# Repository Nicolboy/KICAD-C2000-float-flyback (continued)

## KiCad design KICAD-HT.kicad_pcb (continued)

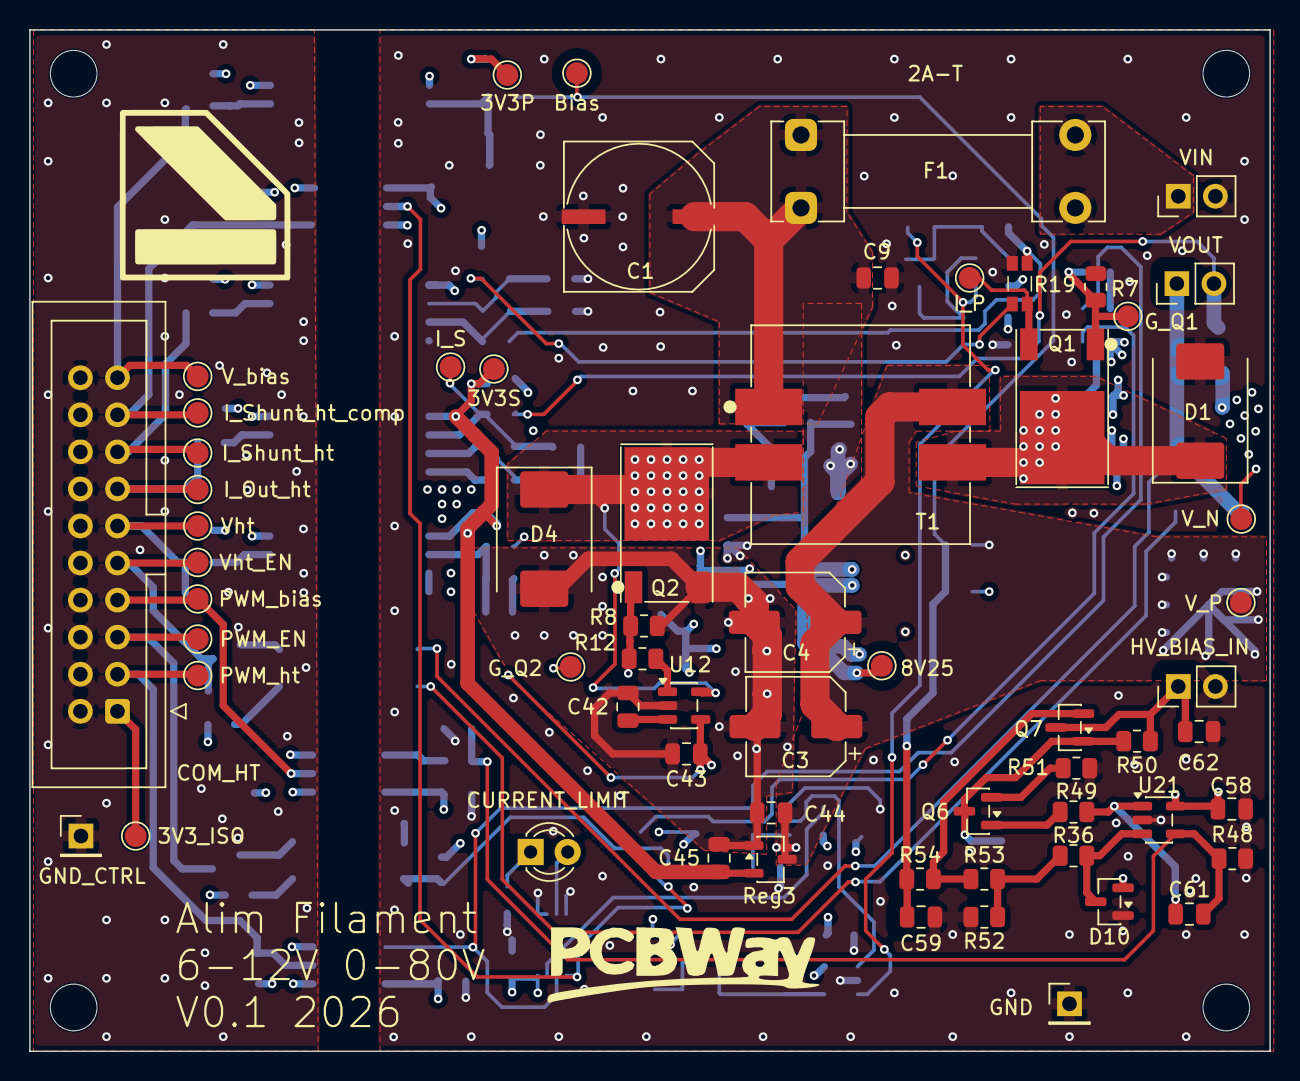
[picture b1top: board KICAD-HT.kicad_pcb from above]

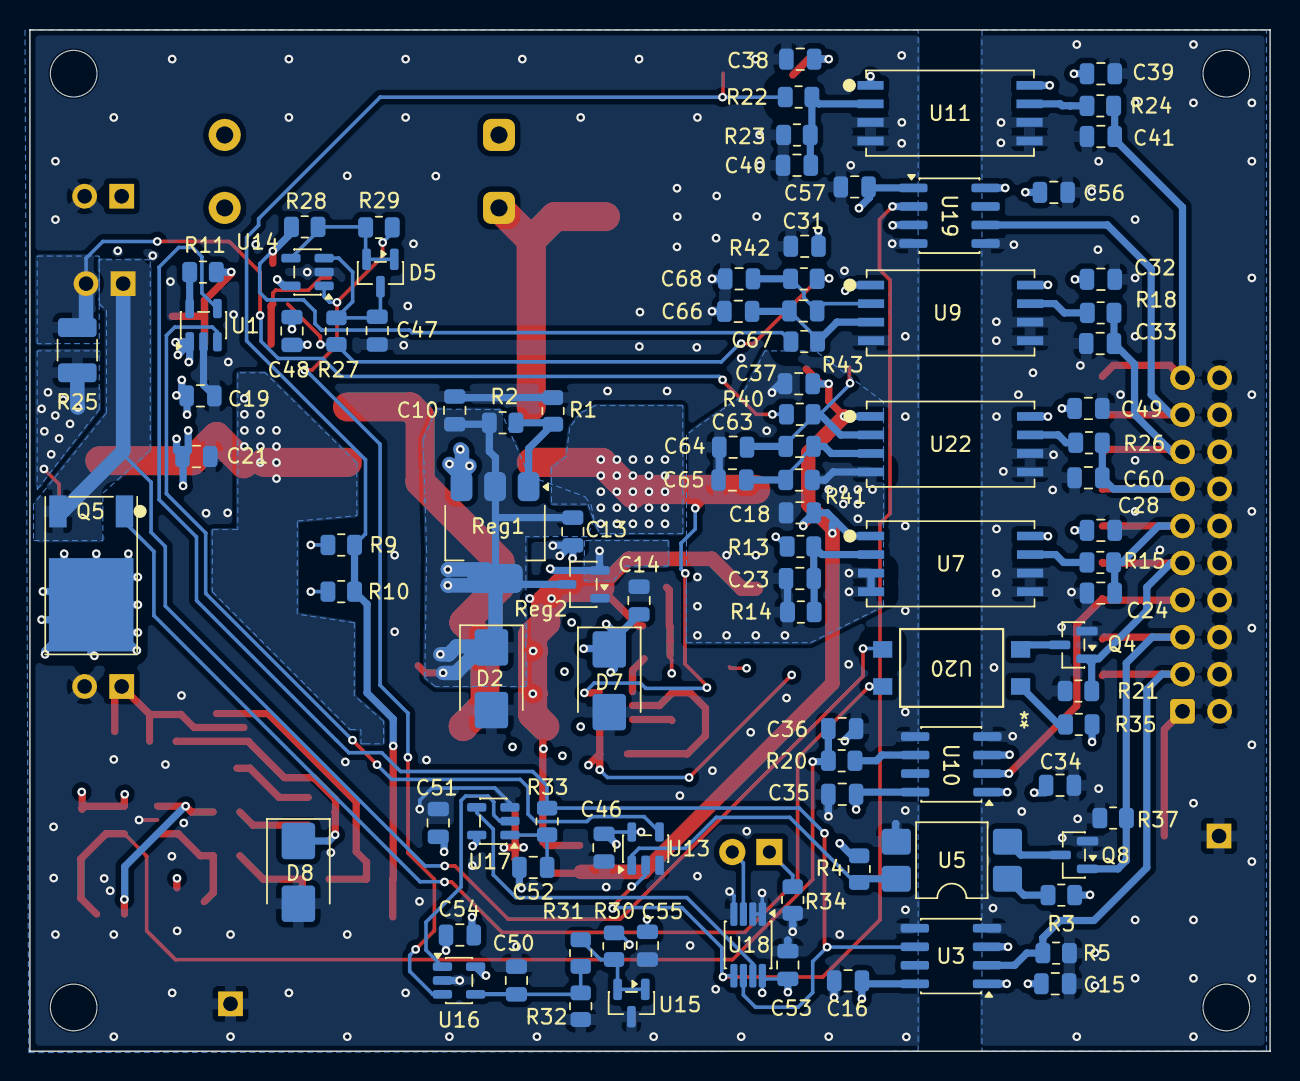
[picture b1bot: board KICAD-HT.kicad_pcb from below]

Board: 4 copper layers, 85.0 x 70.0 mm, 166 parts (99 on the bottom side), 72 nets.

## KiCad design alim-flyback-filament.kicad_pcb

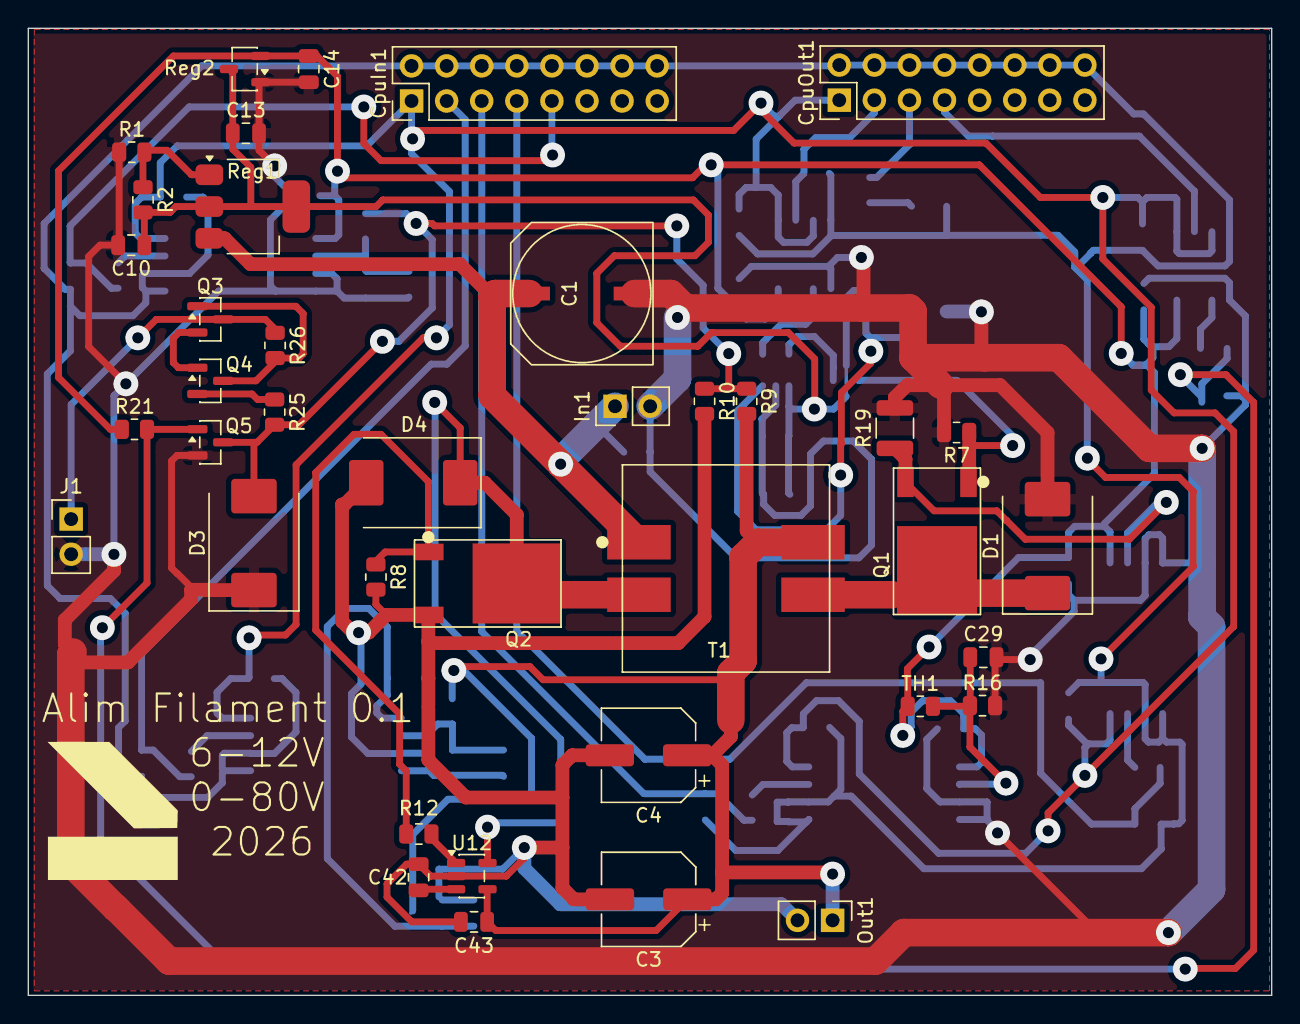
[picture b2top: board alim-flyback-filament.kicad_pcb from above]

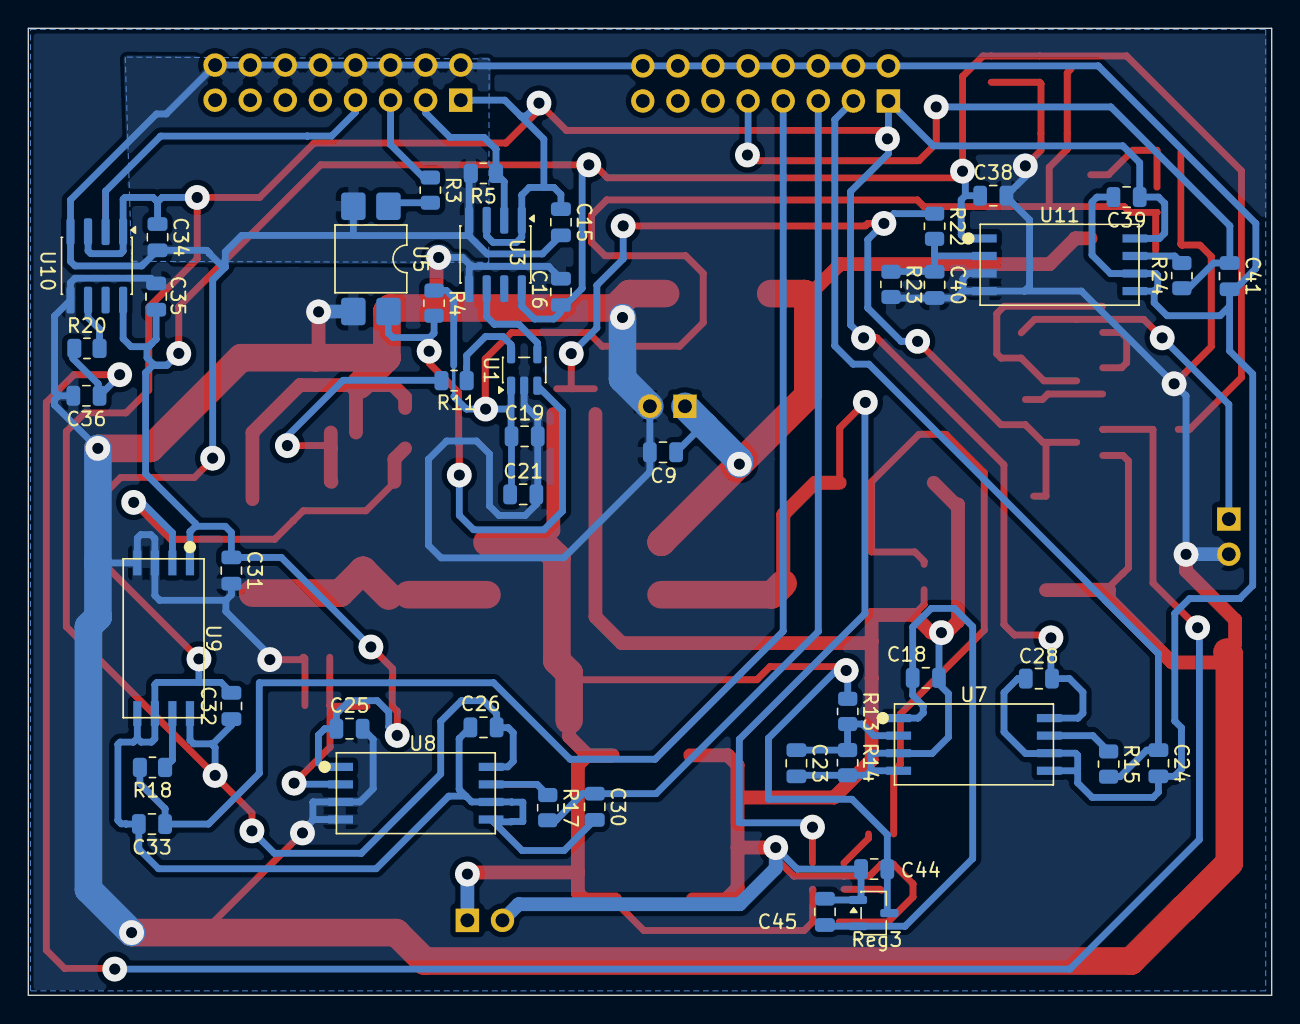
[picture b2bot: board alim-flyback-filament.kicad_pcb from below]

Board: 2 copper layers, 90.0 x 70.0 mm, 85 parts (46 on the bottom side), 42 nets.

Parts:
C1: 470u; A786MW_VChip
C3, C4: 330u; CP_Elec_6.3x9.9
C9, C13, C14, C44, C45: 1u; C_0805_2012Metric
C10, C21, C42: 10u; C_0805_2012Metric
C15, C16, C18, C19, C25, C26, C28, C31, C32, C34, C35, C36, C38, C39, C43: 100n; C_0805_2012Metric
C23, C29, C40: 100p; C_0805_2012Metric
C24, C30, C33, C41: 1n; C_0805_2012Metric
CpuIn1: CTRL_C2000_IN; PinHeader_2x08_P2.54mm_Vertical
CpuOut1: CTRL_C2000_OUT; PinHeader_2x08_P2.54mm_Vertical
D1: SMCJ43A; D_SMC
D3: SMCJ100A; D_SMC
D4: SMCJ54A; D_SMC
In1: VIN; PinHeader_1x02_P2.54mm_Vertical
J1: HV80_IN; PinHeader_1x02_P2.54mm_Vertical
Out1: VOUT; PinHeader_1x02_P2.54mm_Vertical
Q1, Q2: IPD050N10N5; TO252-3_TabPin2
Q3, Q5: BSS127I; SOT-23
Q4: MMBT2222; SOT-23
R1, R15, R17, R18, R24: 100; R_0805_2012Metric
R2: 560; R_0805_2012Metric
R3: 470; R_0805_2012Metric
R4, R14, R16, R20, R23: 10k; R_0805_2012Metric
R5, R7, R8, R9, R10: 100k; R_0805_2012Metric
R11, R12: 1; R_0805_2012Metric
R13: 51k; R_0805_2012Metric
R19: 7m5; R_1210_3225Metric
R21: 1M; R_0805_2012Metric
R22: 470k; R_0805_2012Metric
R25: 2k; R_0805_2012Metric
R26: 75k; R_0805_2012Metric
Reg1: LM317M; SOT-223-3_TabPin2
Reg2, Reg3: MCP1703-3302; SOT-23-3
T1: MSD1514-103ME; MSD1514
TH1: 10k_B4000; R_0805_2012Metric
U1: UCC27517; SOT-23-5
U3, U10: ISO7710; SOIC-8_3.9x4.9mm_P1.27mm
U5: DPC817; SMDIP-4_W7.62mm
U7, U8, U11: AMC0311R; SOIC-8_DWV_5.85x11.5mm_P1.27mm
U9: AMC0302R; SOIC-8_DWV_5.85x11.5mm_P1.27mm
U12: UCC24612; SOT-23-5

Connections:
3V3_CTRL: C15.1, C26.1, C28.1, C32.1, C34.1, C39.1, CpuIn1.1, CpuOut1.1, U3.1 (VCC1), U3.3 (VCC1), U7.8 (VDD2), U8.8 (VDD2), U9.8 (VDD2), U10.1 (VCC1), U10.3 (VCC1), U11.8 (VDD2)
BIAS_FBACK: C41.1, CpuIn1.9, R24.1
BIAS_SENSE: C40.1, R22.2, R23.1, U11.2 (INP)
CS_EMIT: Q4.2 (E), R25.1
CS_GATE: Q3.1 (G), Q4.3 (C), R26.2
CS_TOP: Q3.2 (S), Q4.1 (B)
EN_PRI_IN: CpuOut1.5, R3.1
EN_PRI_OUT: R4.2, U1.3 (IN+), U5.4
GATE_Q1: Q1.1 (G), R7.1, R11.2
GATE_Q2: Q2.1 (G), R8.1, R12.2
GND: C1.2, C9.2, C10.2, C13.2, C14.2, C16.2, C19.2, C21.2, C25.2, C29.2, C31.2, C35.2, C36.2, C38.2, C40.2, D1.2 (A2), D3.1 (A1), In1.2, J1.2, Q5.2 (S), R1.1, R7.2, R16.2, R19.2, R23.2, Reg2.1 (GND), U1.2 (GND), U3.5 (GND2), U5.3, U8.3 (SNSN), U8.4 (GND1), U9.3 (INN), U9.4 (GND1), U10.5 (GND2), U11.3 (SNSN), U11.4 (GND1)
GND_CTRL: C15.2, C24.2, C26.2, C28.2, C30.2, C32.2, C33.2, C34.2, C39.2, C41.2, CpuIn1.2, CpuIn1.4, CpuIn1.6, CpuIn1.8, CpuIn1.10, CpuIn1.12, CpuIn1.14, CpuIn1.16, CpuOut1.2, CpuOut1.4, CpuOut1.6, CpuOut1.8, CpuOut1.10, CpuOut1.12, CpuOut1.14, CpuOut1.16, R5.2, U3.4 (GND1), U5.2, U7.5 (GND2), U7.6 (REFIN), U8.5 (GND2), U8.6 (REFIN), U9.5 (GND2), U9.6 (REFIN), U10.4 (GND1), U11.5 (GND2), U11.6 (REFIN)
HV80_IN: J1.1, Q3.3 (D), R26.1
HV_BIAS: D3.2 (A2), Q5.3 (D), R9.1, R10.1, R22.1, R25.2
ISENSE_P: Q1.3 (S), R19.1, U9.2 (INP)
ISENSE_PRI_FBACK: C33.1, CpuIn1.7, R18.2
unnamed: R3.2, U5.1
unnamed: R1.2, R2.1, Reg1.1 (ADJ)
unnamed: R11.1, U1.5 (OUT)
unnamed: R17.1, U8.7 (OUT)
unnamed: R18.1, U9.7 (OUT)
unnamed: R20.2, U10.6 (OUT)
unnamed: R24.2, U11.7 (OUT)
unnamed: R12.1, U12.1 (VG)
PWM_BIAS_IN: CpuOut1.7, U10.2 (IN)
PWM_PRI_IN: CpuOut1.3, R5.1, U3.2 (IN)
PWM_PRI_OUT: U1.4 (IN-), U3.6 (OUT)
RAIL_3V3_PRI: C14.1, C16.1, C25.1, C31.1, C35.1, C38.1, R21.1, Reg2.2 (VO), TH1.1, U3.8 (VCC2), U8.1 (VDD1), U9.1 (VDD1), U10.8 (VCC2), U11.1 (VDD1)
RAIL_3V3_SEC: C18.1, C45.1, Reg3.2 (VO), U7.1 (VDD1)
RAIL_8V25: C10.1, C13.1, C19.1, C21.1, R2.2, R4.1, Reg1.2 (VO), Reg2.3 (VI), U1.1 (VDD)
REG_SR: C42.2, U12.3 (REG)
SW_PRI: D1.1 (A1), Q1.2 (D), T1.3 (L1.2)
SW_SEC: D4.1 (A1), Q2.2 (D), T1.2 (L2.1), U12.5 (VD)
TEMP: C29.1, R16.1, TH1.2, U8.2 (INP)
TEMP_PRI_FBACK: C30.1, CpuIn1.5, R17.2
VAR_GATE: C36.1, Q5.1 (G), R20.1, R21.2
VIN: C1.1, C9.1, In1.1, Reg1.3 (VI), T1.1 (L1.1)
VOUT_FBACK: C24.1, CpuIn1.3, R15.2
VOUT_FBACK_RAW: R15.1, U7.7 (OUT)
VOUT_N: C3.2, C4.2, C18.2, C23.2, C42.1, C43.1, C44.2, C45.2, D4.2 (A2), Out1.2, Q2.3 (S), R8.2, R10.2, R14.2, Reg3.1 (GND), U7.3 (SNSN), U7.4 (GND1), U12.2 (VS)
VOUT_P: C3.1, C4.1, C43.2, C44.1, Out1.1, R9.2, R13.1, Reg3.3 (VI), T1.4 (L2.2), U12.4 (VDD)
VOUT_SENSE: C23.1, R13.2, R14.1, U7.2 (INP)

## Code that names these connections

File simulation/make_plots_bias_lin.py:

"""Figure de la linearisation HV_BIAS a partir de results/bias_lin.csv
(donnees reelles issues de LTspice, pas de valeurs inventees). Modeles
generiques/ideaux (U20, Q5) -- voir docstring de gen_bias_lin.py."""
import csv
import matplotlib
matplotlib.use("Agg")
import matplotlib.pyplot as plt

rows = list(csv.DictReader(open("results/bias_lin.csv", encoding="utf-8")))
vg = [float(r["vargate_v"]) for r in rows]
vb = [float(r["hv_bias_v"]) for r in rows]

fig, ax = plt.subplots(figsize=(7, 5))
ax.plot(vg, vb, color="C0", lw=2, label="V(HV_BIAS) simule (LTspice, modeles generiques)")
ax.axvline(0.80, color="gray", ls="--", lw=1, alpha=0.7)
ax.annotate("D3 entre en conduction directe\n(plafonne ~0,8V)",
            (0.80, 40), xytext=(1.1, 45), fontsize=9,
            arrowprops=dict(arrowstyle="->", alpha=0.6))
ax.set_xlabel("VAR_GATE (V)")
ax.set_ylabel("HV_BIAS (V)")
ax.set_title("Linearisation HV_BIAS -- U20 (MCP6001 ideal) + Q5 (BSS127I generique)\n"
             "HV80_IN=80V, R26=100k, R45=1k -- 1ere passe, modeles non constructeur")
ax.set_xlim(0, 3.0)
ax.set_ylim(-2, 85)
ax.grid(alpha=0.3)
ax.legend()
fig.tight_layout()
fig.savefig("plots/bias_lin_transfer.png", dpi=140)
print("Ecrit plots/bias_lin_transfer.png")
